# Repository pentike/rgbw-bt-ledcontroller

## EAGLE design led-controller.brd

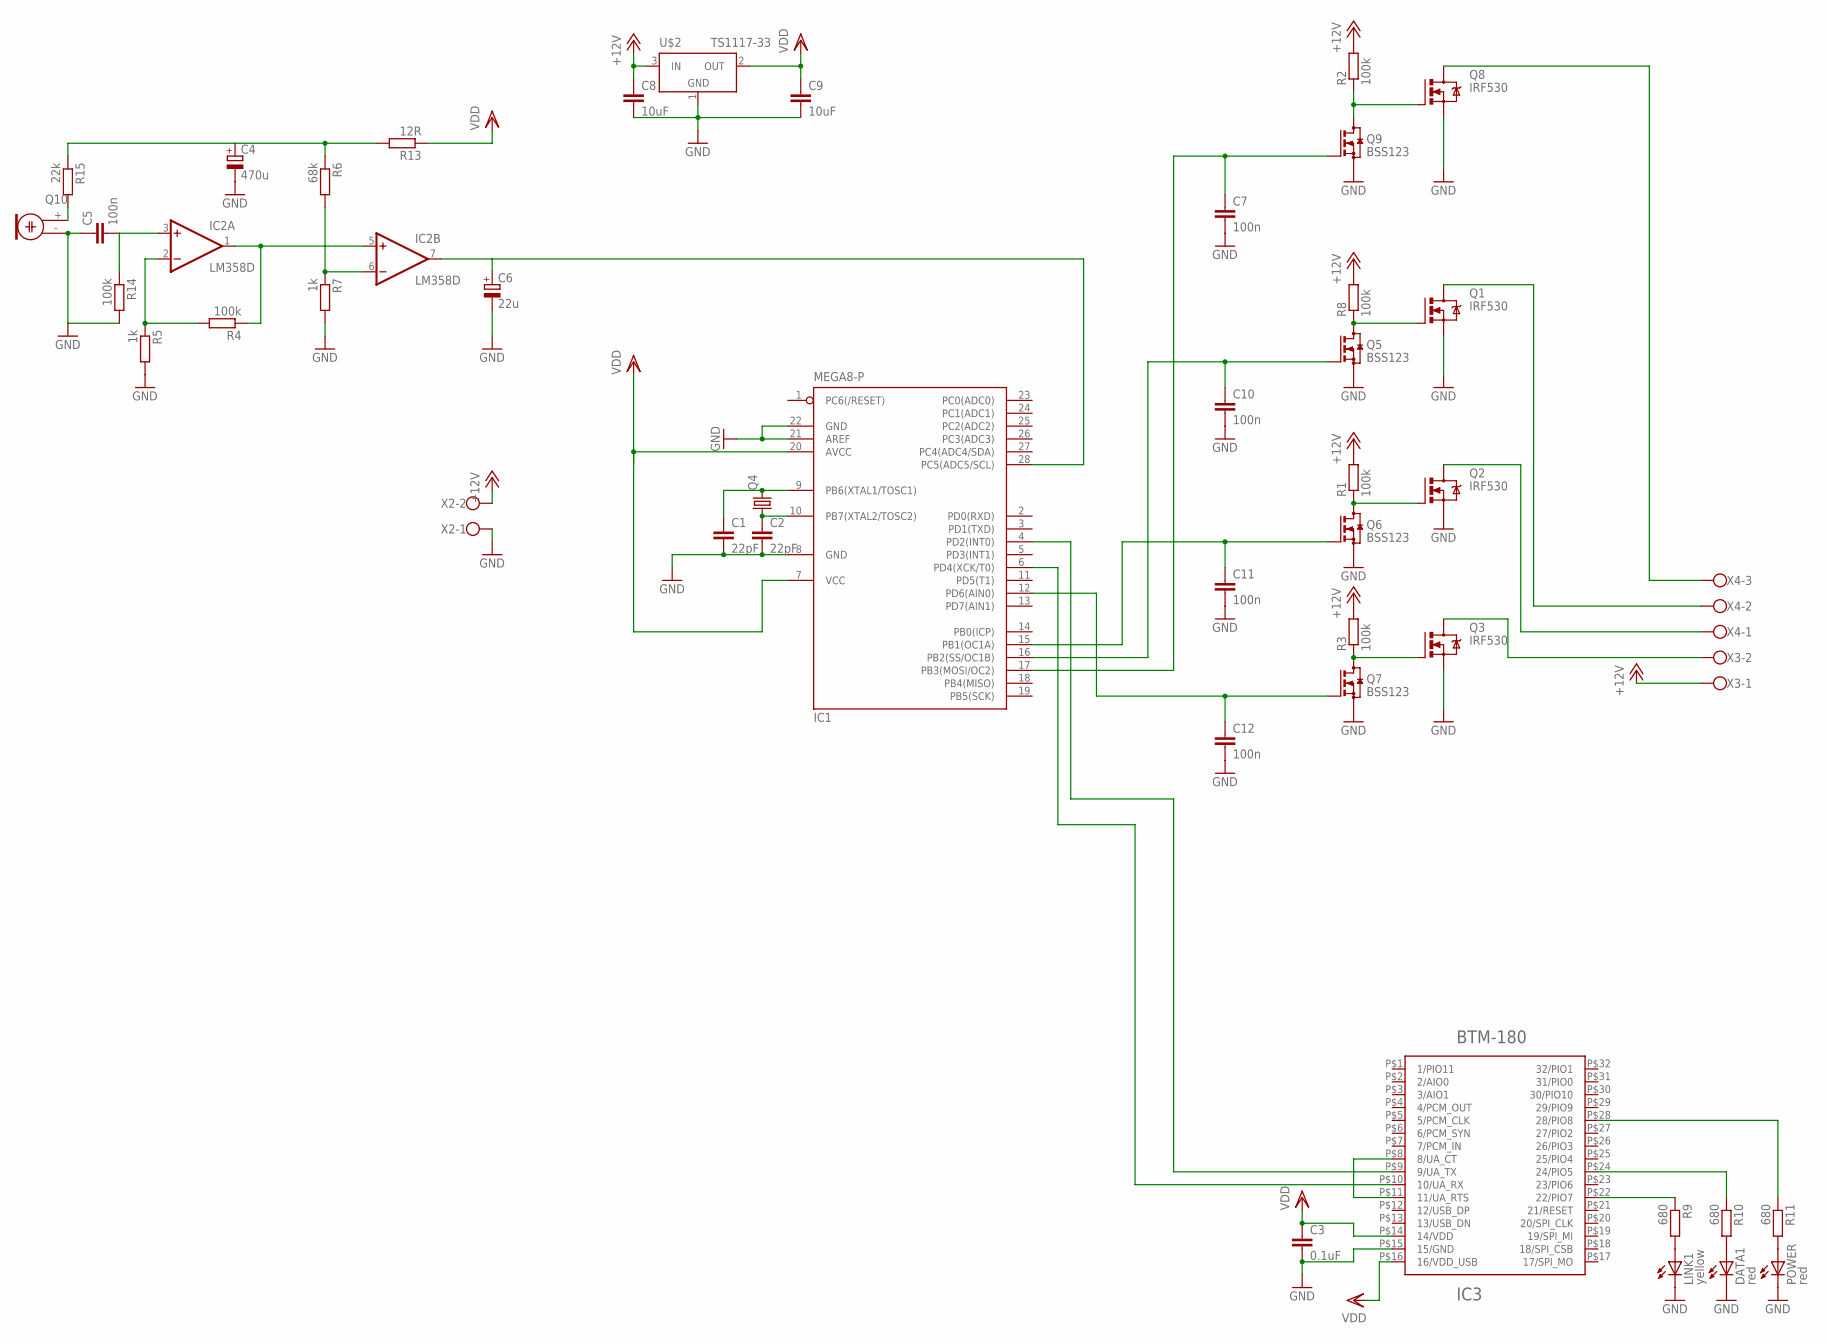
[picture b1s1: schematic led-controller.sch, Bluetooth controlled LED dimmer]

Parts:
C1, C2: 22pF; C0805K
C3: 0.1uF; C0805K
C4: 470u; E2-4
C5, C7, C10, C11, C12: 100n; C0805K
C6: 22u; E2-4
C8, C9: 10uF; C1206K
DATA1: red; CHIPLED_0603; MPN 037107
IC1: MEGA8-P; DIL28-3
IC2: LM358D; SO08
IC3: BTM-180
LINK1: yellow; CHIPLED_0603
POWER: red; CHIPLED_0603
Q1, Q2, Q3, Q8: IRF530; TO220BV
Q4: CRYSTALHC49S; HC49/S
Q5, Q6, Q7, Q9: BSS123; SOT23
Q10: ELECTRET; 9.7ELECTRET
R1, R2, R3, R4, R8, R14: 100k; R0603
R5, R7: 1k; R0603
R6: 68k; R0603
R9, R10, R11: 680; R0603
R13: 12R; R0603
R15: 22k; R0603
U$2: TS1117-33; TO220
X2, X3: W237-102
X4: W237-103

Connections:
+12V: C8.1, R1.2, R2.2, R3.2, R8.2, U$2.3 (IN), X2.2, X3.1
GND: C1.2, C2.2, C3.2, C4.-, C5.1, C6.-, C7.2, C8.2, C9.2, C10.2, C11.2, C12.2, DATA1.C, IC1.8 (GND), IC1.21 (AREF), IC1.22 (GND), IC3.P$15 (15/GND), LINK1.C, POWER.C, Q1.S, Q2.S, Q3.S, Q5.2 (S), Q6.2 (S), Q7.2 (S), Q8.S, Q9.2 (S), Q10.- (1), R5.2, R7.2, R14.2, U$2.1 (GND), X2.1
unnamed: IC2.1 (OUT), IC2.5 (+IN), R4.1
unnamed: C1.1, IC1.9 (PB6(XTAL1/TOSC1)), Q4.2
unnamed: C2.1, IC1.10 (PB7(XTAL2/TOSC2)), Q4.1
unnamed: C11.1, IC1.15 (PB1(OC1A)), Q6.1 (G)
unnamed: C10.1, IC1.16 (PB2(SS/OC1B)), Q5.1 (G)
unnamed: C12.1, IC1.12 (PD6(AIN0)), Q7.1 (G)
unnamed: Q1.G, Q5.3 (D), R8.1
unnamed: Q2.G, Q6.3 (D), R1.1
unnamed: Q3.G, Q7.3 (D), R3.1
unnamed: C7.1, IC1.17 (PB3(MOSI/OC2)), Q9.1 (G)
unnamed: IC2.6 (-IN), R6.2, R7.1
unnamed: Q8.G, Q9.3 (D), R2.1
unnamed: IC2.2 (-IN), R4.2, R5.1
unnamed: C4.+, R6.1, R13.2, R15.1
unnamed: Q10.+ (2), R15.2
unnamed: C5.2, IC2.3 (+IN), R14.1
unnamed: C6.+, IC1.28 (PC5(ADC5/SCL)), IC2.7 (OUT)
unnamed: IC3.P$8 (8/UA_CT), IC3.P$11 (11/UA_RTS)
unnamed: IC1.6 (PD4(XCK/T0)), IC3.P$10 (10/UA_RX)
unnamed: IC1.4 (PD2(INT0)), IC3.P$9 (9/UA_TX)
unnamed: POWER.A, R11.2
unnamed: DATA1.A, R10.2
unnamed: LINK1.A, R9.2
unnamed: IC3.P$22 (22/PIO7), R9.1
unnamed: IC3.P$24 (24/PIO5), R10.1
unnamed: IC3.P$28 (28/PIO8), R11.1
OUT$BLUE: Q3.D, X3.2
OUT$BLUE1: Q8.D, X4.3
OUT$GREEN: Q2.D, X4.1
OUT$RED: Q1.D, X4.2
V+: IC2.8 (V+)
V-: IC2.4 (V-)
VDD: C3.1, C9.1, IC1.7 (VCC), IC1.20 (AVCC), IC3.P$14 (14/VDD), IC3.P$16 (16/VDD_USB), R13.1, U$2.2 (OUT)

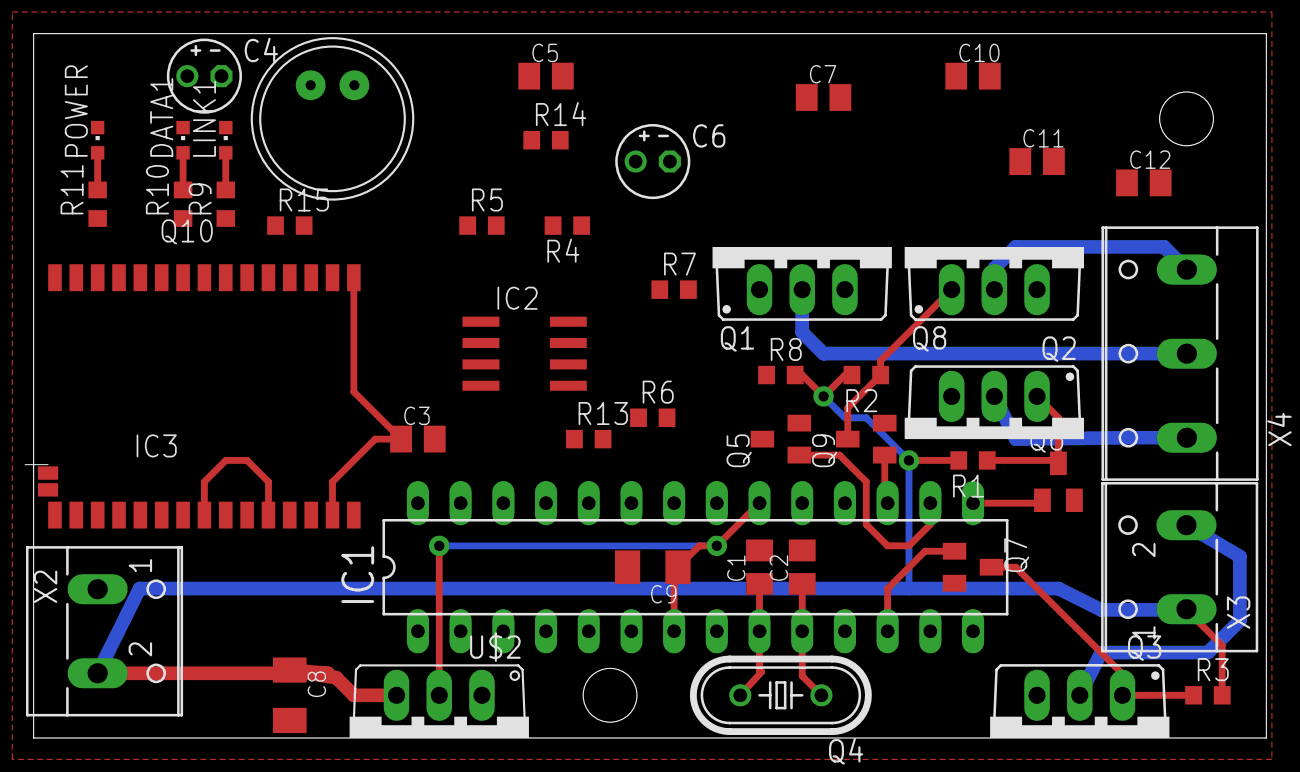
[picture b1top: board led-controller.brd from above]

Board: 2 copper layers, 73.3 x 41.9 mm, 46 parts (0 on the bottom side), 33 nets.

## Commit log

2014-06-16 Initial commit, this stuff does not work.
